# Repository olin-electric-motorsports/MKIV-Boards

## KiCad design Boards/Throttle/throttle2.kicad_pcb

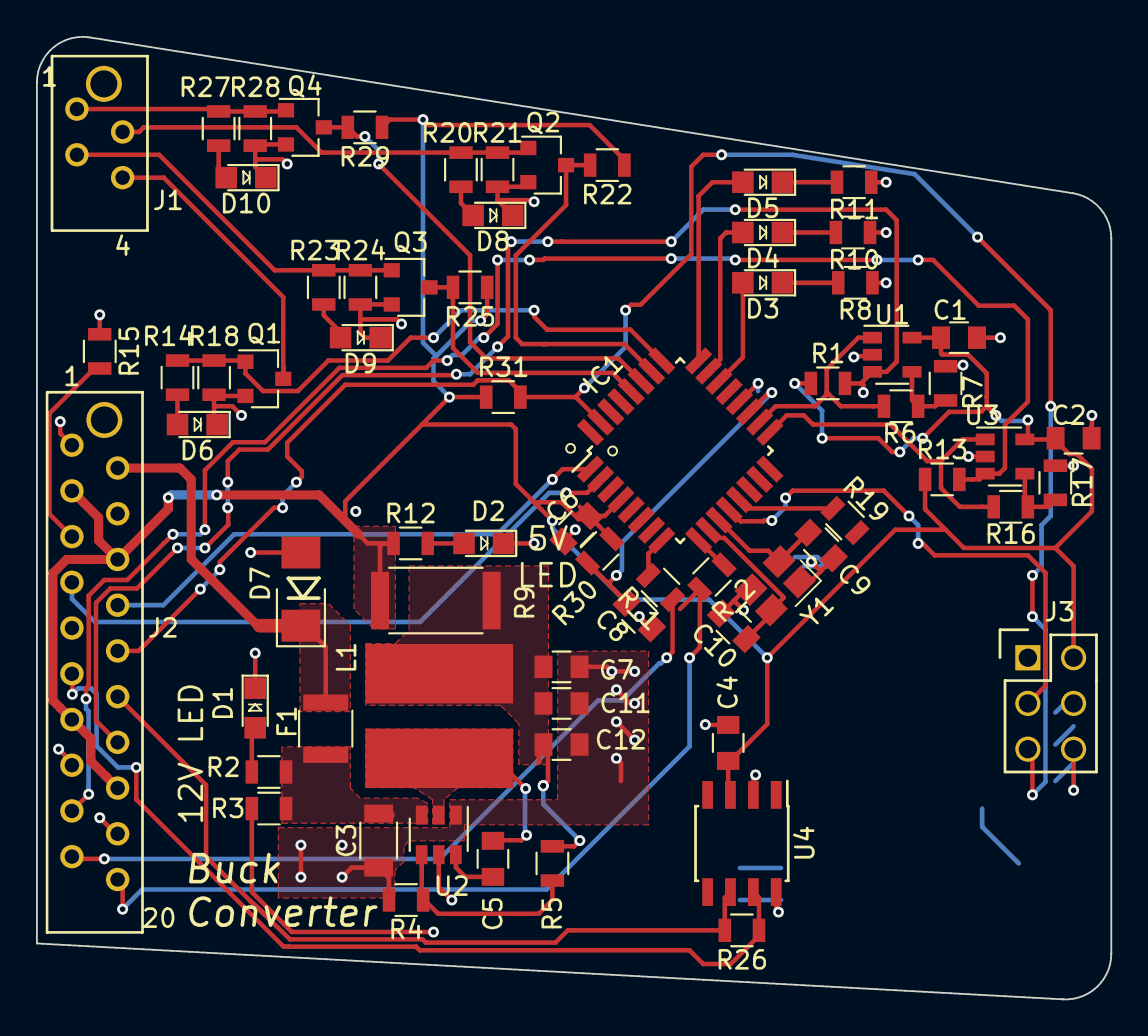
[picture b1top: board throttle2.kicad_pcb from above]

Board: 2 copper layers, 59.7 x 53.5 mm, 70 parts (0 on the bottom side), 52 nets.

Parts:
C1, C2, C4, C5, C6, C7: C_0.1uF; C_0805_OEM
C3: C_22uF; C_1206_OEM
C8: C_100pF; C_0805_OEM
C9, C10: C_30pF; C_0805_OEM
C11: C_1uF; C_0805_OEM
C12: C_47uF; C_0805_OEM
D1, D2, D3, D4, D5, D6, D8, D9, D10: LED_0805; LED_0805_OEM
D7: D_Zener_18V; DO-214AA
F1: 500mA; Fuse_1210
IC1: ATMEGA16M1; TQFP-32_7x7mm_Pitch0.8mm
J1: micromatch_female_TOP_ENTRY_locking_4; micromatch_female_vert_4
J2: micromatch_female_TOP_ENTRY_locking_20; micromatch_female_vert_20
J3: CONN_02X03; Pin_Header_Straight_2x03
L1: L_4.7uH; 4.7uH_Inductor_OEM
Q1, Q2, Q3, Q4: SSM3K333R; SOT-23F
R1, R13: R_1M; R_0805_OEM
R2, R6, R20, R23, R27: R_1k; R_0805_OEM
R3, R4, R22, R25, R29, R31: R_10k; R_0805_OEM
R5: R_51.1k; R_0805_OEM
R7, R16, R17: R_2.2k; R_0805_OEM
R8, R10, R11, R12, R14: R_200; R_0805_OEM
R9: R_0_Jumper; R_2512_OEM
R15, R19: R_22K; R_0805_OEM
R18: R_100K; R_0805_OEM
R21, R24, R28: R_100k; R_0805_OEM
R26: R_120 DNP; R_0805_OEM
R30: R_100; R_0805_OEM
R_1, R_2: R_200; R_0805_OEM
U1, U3: MCP6001; SOT-23-5_OEM
U2: TPS561201; SOT-23-6_OEM
U4: CAN_Transceiver; SOIC-8_3.9x4.9mm_Pitch1.27mm_OEM
Y1: Crystal_SMD; Crystal_SMD_FA238

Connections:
+12V: D7.1, F1.1, J2.2
/12V_Fused: C3.1, F1.2, R2.1, R3.1, U2.3
/CANH: J2.11, R26.1, U4.7
/CANL: J2.12, R26.2, U4.6
/Drive_Mode_Out: IC1.13, J2.4, R19.1
/GND_DriveMode: J2.5, R15.2
/LED1: J2.19, R_1.1
/LED2: J2.20, R_2.1
/MISO: IC1.1, J2.8, J3.1
/MOSI: IC1.2, J2.7, J3.4
/ProgrammingLED1: D3.2, IC1.22
/ProgrammingLED2: D4.2, IC1.23
/ProgrammingLED3: D5.2, IC1.24
/RESET: IC1.31, J2.10, J3.5, R31.2
/RTD: J1.4, Q1.3
/RXCAN: IC1.7, U4.4
/ReadyToDrive_LowDrive: IC1.25, Q1.1, R14.1, R18.1
/SCK: IC1.12, J2.9, J3.3
/SS_BOTS: J1.1, Q4.1, R27.1, R28.1
/SS_BOTS_Out_n: IC1.27, Q4.3, R29.2
/SS_Cockpit_EStop: J1.3, Q3.1, R23.1, R24.1
/SS_EStop_Out_n: IC1.28, Q3.3, R25.2
/SS_Inertia_Out_n: IC1.26, Q2.3, R22.2
/SS_Inertia_Switch: J1.2, Q2.1, R20.1, R21.1
/TXCAN: IC1.6, U4.1
/Throttle1Adjusted: IC1.17, R16.1, U3.1
/Throttle1_Right_Sense: J2.14, R1.2, U1.3
/Throttle2Adjusted: IC1.18, R6.1, U1.1
/Throttle2_Left_Sense: J2.17, R13.2, U3.3
GND: C1.1, C2.1, C3.2, C4.2, C6.2, C7.2, C8.2, C9.2, C10.2, C11.2, C12.2, D1.1, D2.1, D6.1, D7.2, D8.1, D9.1, D10.1, IC1.5, IC1.20, J2.1, J2.15, J2.18, J3.6, Q1.2, Q2.2, Q3.2, Q4.2, R4.2, R7.2, R8.2, R10.2, R11.2, R15.1, R17.2, R18.2, R19.2, R21.2, R24.2, R28.2, U1.2, U2.1, U3.2, U4.2, U4.8, Y1.2, Y1.4
unnamed: C5.1, U2.6
unnamed: C5.2, L1.1, U2.2
unnamed: C8.1, IC1.19, R30.2
unnamed: C9.1, IC1.11, Y1.1
unnamed: C10.1, IC1.10, Y1.3
unnamed: C7.1, C11.1, C12.1, L1.2, R5.2, R9.2
unnamed: D1.2, R2.2
unnamed: D2.2, R12.2
unnamed: D3.1, R8.1
unnamed: D4.1, R10.1
unnamed: D5.1, R11.1
unnamed: D6.2, R14.2
unnamed: D8.2, R20.2
unnamed: D9.2, R23.2
unnamed: D10.2, R27.2
unnamed: IC1.8, R_1.2
unnamed: IC1.9, R_2.2
unnamed: R3.2, U2.5
unnamed: R4.1, R5.1, U2.4
unnamed: R6.2, R7.1, U1.4
unnamed: R16.2, R17.1, U3.4
VCC: C1.2, C2.2, C4.1, C6.1, IC1.4, J2.3, J2.6, J2.13, J2.16, J3.2, R1.1, R9.1, R12.1, R13.1, R22.1, R25.1, R29.1, R30.1, R31.1, U1.5, U3.5, U4.3

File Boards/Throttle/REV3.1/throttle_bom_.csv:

Component,Description,Part,References,Value,Footprint,Quantity Per PCB,Datasheet,Package,MPN,MFN,PurchasingLink,Purchase_Link
1,"Capacitor, 0.1uF, 50V, 5%, 0805",C_0.1uF,C1 C2 C4 C5 C6 C7,C_0.1uF,C_0805_OEM,6,http://datasheets.avx.com/X7RDielectric.pdf,Value,478-3352-1-ND,DK,https://www.digikey.com/products/en?keywords=478-3352-1-ND,
2,"Capacitor, 100pF, 50V, 5%, 0805",C_100pF,C8,C_100pF,C_0805_OEM,1,https://katalog.we-online.de/pbs/datasheet/885012007057.pdf,Value,732-7852-1-ND,DK,https://www.digikey.com/product-detail/en/wurth-electronics-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,
3,"Capacitor, 1uF, 25V, 10%, 0805",C_1uF,C11,C_1uF,C_0805_OEM,1,http://www.samsungsem.com/kr/support/product-search/mlcc/__i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,Value,1276-2887-1-ND,DK,https://www.digikey.com/product-detail/en/samsung-electro-me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,
4,"Capacitor, 22uF, 16V, 20%, 1206",C_22uF,C3,C_22uF,C_1206_OEM,1,https://product.tdk.com/info/en/catalog/datasheets/mlcc_comm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,Value,445-11693-1-ND,DK,https://www.digikey.com/product-detail/en/tdk-corporation/C3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,
5,"Capacitor, 30pF, 50V, 5%, 0805",C_30pF,C9 C10,C_30pF,C_0805_OEM,2,https://media.digikey.com/pdf/Data%20Sheets/Samsung%20PDFs/C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,Value,1276-1130-1-ND,DK,https://www.digikey.com/product-detail/en/samsung-electro-me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,
6,"Capacitor, 47uF, 6.3V, 20%, 0805",C_47uF,C12,C_47uF,C_0805_OEM,1,http://www.samsungsem.com/kr/support/product-search/mlcc/__i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,Value,1276-6467-1-ND,DK,https://www.digikey.com/product-detail/en/samsung-electro-me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,
7,"Diode, Zener, 18V, 5W, 5%",D_Zener_18V,D7,D_Zener_18V,DO-214AA,1,http://www.mccsemi.com/up_pdf/SMBJ5338B-SMBJ5388B(SMB).pdf,DO-214AA (SMB),SMBJ5355B-TPMSCT-ND,DK,https://www.digikey.com/products/en?keywords=SMBJ5355B-TPMSCT-ND,
8,"LED, Green, 2.2V, 20mA, 0805",LED_0805,D1 D2 D3 D4 D5 D6 D8 D9 D10,LED_0805,LED_0805_OEM,9,http://www.osram-os.com/Graphics/XPic9/00078860_0.pdf,Value,475-1410-1-ND,DK,https://www.digikey.com/products/en?keywords=475-1410-1-ND,
9,"Fuse, PTC, 500mA, 16V, 1210",F_500mA_16V,F1,500mA,Fuse_1210,1,https://belfuse.com/resources/CircuitProtection/datasheets/0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,Value,507-1786-1-ND,DK,https://www.digikey.com/product-detail/en/bel-fuse-inc/0ZCH0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,
10,"Microcontroller, 8-bit, 1KB RAM, 16KB Flash",ATMEGA16M1,IC1,ATMEGA16M1,TQFP-32_7x7mm_Pitch0.8mm,1,http://ww1.microchip.com/downloads/en/DeviceDoc/Atmel-8209-8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,Value,ATMEGA16M1-AU-ND,DK,https://www.digikey.com/product-detail/en/atmel/ATMEGA16M1-A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,
11,"Connector header through hole 2x3 0.100"" (2.54mm)",CONN_02X03,J3,CONN_02X03,Pin_Header_Straight_2x03,1,http://portal.fciconnect.com/Comergent//fci/drawing/67996.pdf,Value,609-3234-ND,DK,https://www.digikey.com/product-detail/en/amphenol-fci/67997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,
12,Micro-MaTch connector 20 pin female vertical,MM_F_VT_20,J2,micromatch_female_TOP_ENTRY_locking_20,micromatch_female_vert_20,1,http://www.te.com/commerce/DocumentDelivery/DDEController?Ac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,Value,2-338068-0,TE,http://www.te.com/global-en/product-2-338068-0.html,
13,Micro-MaTch connector 4 pin female vertical,MM_F_VT_04,J1,micromatch_female_TOP_ENTRY_locking_4,micromatch_female_vert_4,1,http://www.te.com/commerce/DocumentDelivery/DDEController?Ac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,Value,338068-4,TE,http://www.te.com/global-en/product-338068-4.html,
14,"Inductor, 4.7uH, 4.4A, 25mOhm, 20%",L_4.7uH,L1,L_4.7uH,4.7uH_Inductor_OEM,1,https://product.tdk.com/info/en/documents/wdcatalog/withdraw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,Value,445-6583-1-ND,DK,https://www.digikey.com/product-detail/en/tdk-corporation/VL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,
15,"MOSFET, N-channel, 30V, 6A",SSM3K333R,Q1 Q2 Q3 Q4,SSM3K333R,SOT-23F,4,https://drive.google.com/drive/folders/0B-V-iZf33Y4GNzhDQTJZanJRbVk,SOT-23-3 Flat Leads,SSM3K333RLFCT-ND,DK,https://www.digikey.com/product-detail/en/toshiba-semiconduc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,https://www.digikey.com/product-detail/en/toshiba-semiconduc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
16,"Resistor, 0 ohm jumper, 0.1W, 0603",R_0,R9,R_0_Jumper,R_0603_1608Metric,1,http://industrial.panasonic.com/www-cgi/jvcr13pz.cgi?E+PZ+3+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,Value,P0.0GCT-ND,DK,https://www.digikey.com/product-detail/en/panasonic-electron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,
17,"Resistor, 100, 0.25W, 1%, 0805",R_100,R30,R_100,R_0805_OEM,1,https://www.seielect.com/Catalog/SEI-rncp.pdf,Value,RNCP0805FTD100RCT-ND,DK,https://www.digikey.com/products/en?keywords=RNCP0805FTD100RCT-ND,
18,"Resistor, 100K, 0.125W, 1%, 0805",R_100K,R18 R21 R24 R28,R_100K,R_0805_OEM,4,https://industrial.panasonic.com/cdbs/www-data/pdf/RDA0000/A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,Value,P100KCCT-ND,DK,https://www.digikey.com/product-detail/en/panasonic-electron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,
19,"Resistor, 10K, 0.25W, 1%, 0805",R_10K,R22 R25 R29 R31,R_10k,R_0805_OEM,4,http://www.bourns.com/data/global/pdfs/CRS.pdf,Value,CRS0805-FX-1002ELFCT-ND,DK,https://www.digikey.com/products/en?keywords=CRS0805-FX-1002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,
20,"Resistor, 10K, 5W, 1%, Axial",R_10K_HV,R3 R4,R_10k,R_0805_OEM,2,http://www.vishay.com/docs/28731/pacserie.pdf,Value,PPC5D10.0KCT-ND,DK,https://www.digikey.com/products/en?keywords=PPC5D10.0KCT-ND,
21,"Resistor, 120K, 0.125W, 1%, 0805",R_120K,R26,R_120 DNP,R_0805_OEM,1,https://www.seielect.com/Catalog/SEI-RMCF_RMCP.pdf,Value,RMCF0805JT200RCT-ND,DK,https://www.digikey.com/products/en?keywords=RMCF0805JT200RCT-ND,
22,"Resistor, 1M, 0.125W, 5%, 0805",R_1M,R1 R13,R_1M,R_0805_OEM,2,https://www.seielect.com/Catalog/SEI-rncp.pdf,Value,RMCF0805JT1M00CT-ND,DK,https://www.digikey.com/product-detail/en/stackpole-electron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,
23,"Resistor, 1K, 0.25W, 1%, 0805",R_1K,R2 R6 R20 R23 R27,R_1k,R_0805_OEM,5,https://www.seielect.com/Catalog/SEI-rncp.pdf,Value,RNCP0805FTD1K00CT-ND,DK,https://www.digikey.com/products/en?keywords=RNCP0805FTD1K00CT-ND,
24,"Resistor, 2.2K, 0.125W, 1%, 0805",R_2.2K,R7 R16 R17,R_2.2k,R_0805_OEM,3,https://www.seielect.com/Catalog/SEI-RMCF_RMCP.pdf,Value,RMCF0805FT2K20CT-ND,DK,https://www.digikey.com/product-detail/en/stackpole-electron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,
25,"Resistor, 200, 0.125W, 5%, 0805",R_200,R8 R10 R11 R12 R14 R_1 R_2,R_200,R_0805_OEM,7,https://www.seielect.com/Catalog/SEI-RMCF_RMCP.pdf,Value,RMCF0805JT200RCT-ND P100KCCT-ND,DK,https://www.digikey.com/products/en?keywords=RMCF0805JT200RCT-ND https://www.digikey.com/product-detail/en/panasonic-electron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,
26,"Resistor, 22K, 0.125W, 5%, 0805",R_22K,R15 R19,R_22K,R_0805_OEM,2,https://www.seielect.com/Catalog/SEI-RMCF_RMCP.pdf,,RMCF0805JT22K0CT-ND,DK,https://www.digikey.com/products/en?keywords=RMCF0805JT22K0CT-ND,
27,"Resistor, 51.1K, 0.125W, 1%, 0805",R_51.1K,R5,R_51.1k,R_0805_OEM,1,https://industrial.panasonic.com/cdbs/www-data/pdf/RDA0000/A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,Value,P51.1KCCT-ND,DK,https://www.digikey.com/product-detail/en/panasonic-electron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,
28,"High speed CAN transceiver, 1Mb/s",MCP2561-E_SN,U4,CAN_Transceiver,SOIC-8_3.9x4.9mm_Pitch1.27mm_OEM,1,http://www.microchip.com/mymicrochip/filehandler.aspx?ddocna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,Value,MCP2561-E/SN-ND,DK,https://www.digikey.com/products/en?keywords=mcp2561-e%2Fsn,
29,"Op-amp, general purpose",MCP6001,U1 U3,MCP6001,SOT-23-5_OEM,2,http://ww1.microchip.com/downloads/en/DeviceDoc/21733j.pdf,Value,MCP6001T-I/OTCT-ND,N/A,https://www.digikey.com/product-detail/en/microchip-technolo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,
30,"Buck converter, 4.5-17V input, adj 0.76-7V output, 1A, 580kHz",TPS561201,U2,TPS561201,SOT-23-6_OEM,1,http://www.ti.com/lit/ds/symlink/tps561201.pdf,Value,TPS561201,DK,https://www.digikey.com/products/en?keywords=296-46928-1-ND,
31,CRYSTAL 16.0000MHZ 18PF SMD,Crystal_SMD,Y1,Crystal_SMD,Crystal_SMD_FA238,1,http://www.txccorp.com/download/products/quartz_crystals/201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,Value,887-1125-1-ND,DK,https://www.digikey.com/product-detail/en/txc-corporation/7M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,





Component Groups:,31
Component Count:,70
Fitted Components:,70
Number of PCBs:,1
Total components:,70
Schematic Version:,
Schematic Date:,
BoM Date:,Sat 01 Dec 2018 11:14:35 AM EST
Schematic Source:,/home/awenstrup/Documents/Formula/MKIV-Boards/Boards/Throttle/REV3.1/throttle.sch
KiCad Version:,Eeschema 5.0.1-33cea8e~68~ubuntu18.04.1

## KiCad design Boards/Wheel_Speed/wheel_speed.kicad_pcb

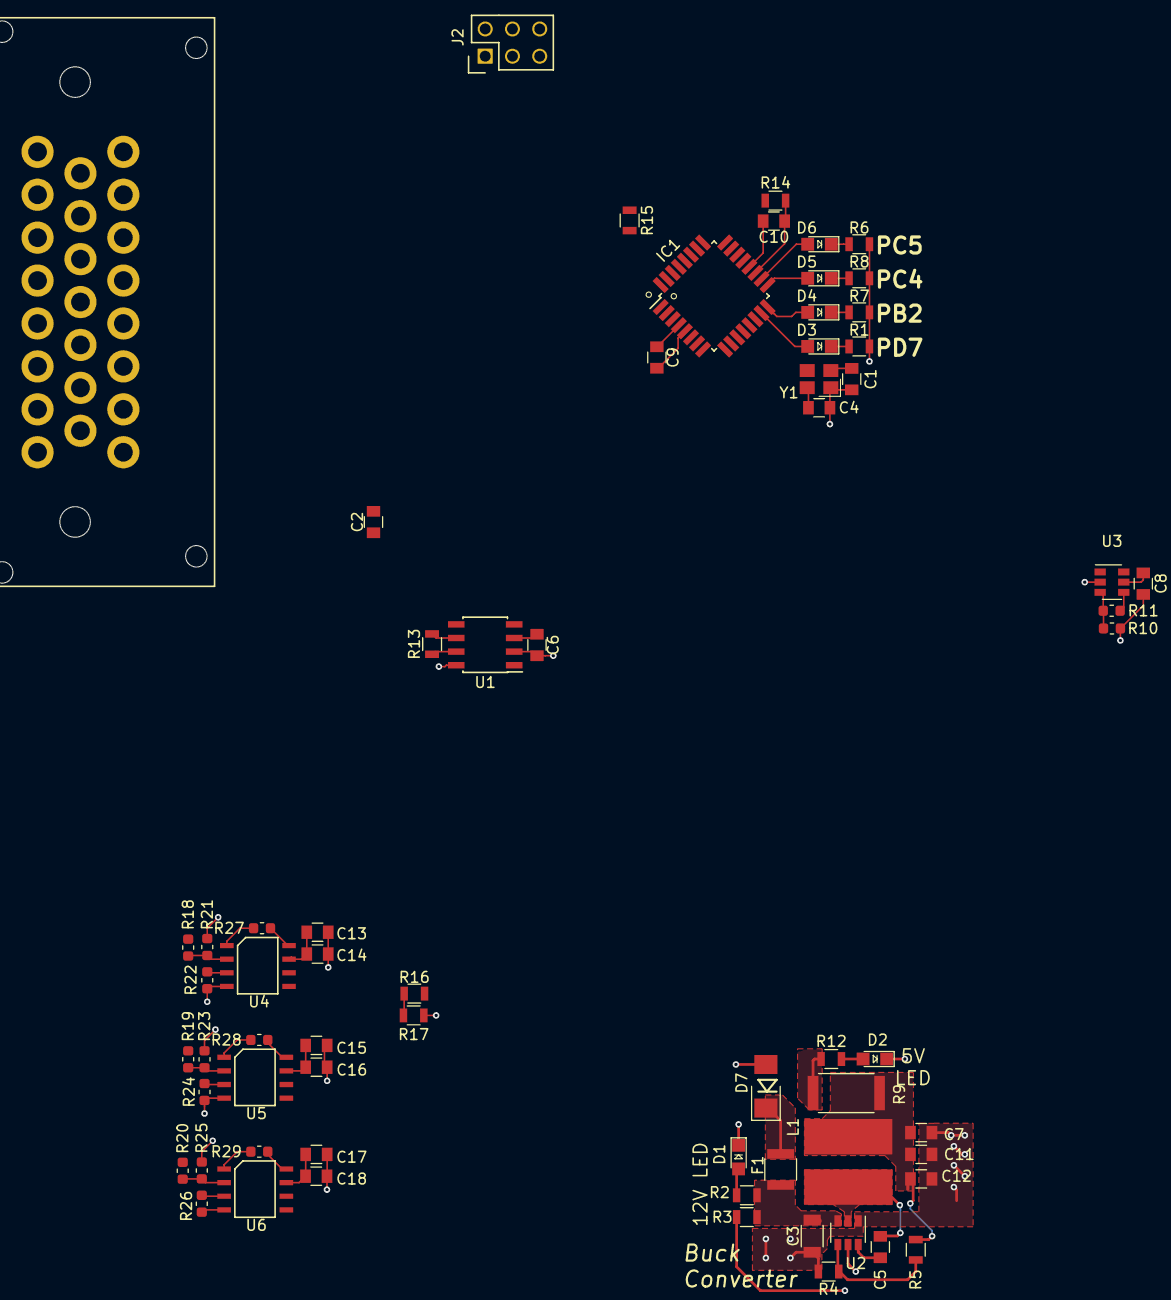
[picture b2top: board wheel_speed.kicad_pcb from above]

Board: 2 copper layers, 66 parts (0 on the bottom side), 51 nets.

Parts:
C1, C4: C_30pF; C_0805_OEM
C2, C5, C6, C8, C9, C12, C14, C16, C18: C_0.1uF; C_0805_OEM
C3: C_22uF; C_1206_OEM
C7: C_47uF; C_0805_OEM
C10: C_100pF; C_0805_OEM
C11: C_1uF; C_0805_OEM
C13, C15, C17: C_10uF; C_0805_OEM
D1, D2, D3, D4, D5, D6: LED_0805; LED_0805_OEM
D7: D_Zener_18V; DO-214AA
F1: 500mA; Fuse_1210
IC1: ATMEGA16M1; TQFP-32_7x7mm_Pitch0.8mm
J1: Ampseal_23_RA; Ampseal_23
J2: CONN_02X03; Pin_Header_Straight_2x03
L1: L_4.7uH; 4.7uH_Inductor_OEM
R1, R6, R7, R8, R12: R_200; R_0805_OEM
R2: R_1k; R_0805_OEM
R3, R4, R15: R_10k; R_0805_OEM
R5: R_51.1k; R_0805_OEM
R9: R_0_Jumper; R_2512_OEM
R10, R11, R18, R19, R20, R21, R22, R23, R24, R25, R26, R27, R28, R29: R_0; R_0603_1608Metric
R13: R_120; R_0805_OEM
R14: R_100; R_0805_OEM
R16, R17: R_10K; R_0805_OEM
U1: CAN_Transceiver; SOIC-8_3.9x4.9mm_Pitch1.27mm_OEM
U2: TPS561201; SOT-23-6_OEM
U3: LMV341; SOT-23-6
U4, U5, U6: AD623; AD623_SOIC-8
Y1: Crystal_SMD; Crystal_SMD_FA238

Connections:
+12V: D7.1, F1.1, J1.1
/12V_Fused: C3.1, F1.2, R2.1, R3.1, U2.3
/BRAKETEMP: IC1.27, J1.12
/CANH: J1.3, J1.17, R13.1, U1.7
/CANL: J1.4, J1.18, R13.2, U1.6
/HSENSOR: IC1.26, J1.13
/MISO: IC1.1, J2.1
/MOSI: IC1.2, J2.4
/POT: J1.11, U3.1
/POT_SIGNAL: IC1.22, R10.1, R11.2, U3.3
/P_LED_1: D3.2, IC1.15
/P_LED_2: D4.2, IC1.16
/P_LED_3: D5.2, IC1.17
/P_LED_4: D6.2, IC1.18
/RESET: IC1.31, J2.5, R15.2
/RXCAN: IC1.7, U1.4
/SCK: IC1.12, J2.3
/Suspension Strain Testing/2.5V: R16.2, R17.1, U4.5, U5.5, U6.5
/TXCAN: IC1.6, U1.1
GND: C1.2, C2.1, C3.2, C4.2, C6.2, C7.2, C8.2, C9.2, C10.2, C11.2, C12.2, C13.1, C14.1, C15.1, C16.1, C17.1, C18.1, D1.1, D2.1, D7.2, IC1.5, IC1.20, J1.2, J1.6, J2.6, R1.2, R4.2, R6.2, R7.2, R8.2, R10.2, R17.2, R21.1, R22.1, R23.1, R24.1, R25.1, R26.1, U1.2, U1.8, U2.1, U3.2, U4.4, U5.4, U6.4, Y1.2, Y1.4
unnamed: C1.1, IC1.11, Y1.1
unnamed: C4.1, IC1.10, Y1.3
unnamed: C5.1, U2.6
unnamed: C5.2, L1.1, U2.2
unnamed: C10.1, IC1.19, R14.2
unnamed: C7.1, C11.1, C12.1, L1.2, R5.2, R9.2
unnamed: D1.2, R2.2
unnamed: D2.2, R12.2
unnamed: D3.1, R1.1
unnamed: D4.1, R7.1
unnamed: D5.1, R8.1
unnamed: D6.1, R6.1
unnamed: R3.2, U2.5
unnamed: R4.1, R5.1, U2.4
unnamed: R11.1, U3.4
unnamed: R18.1, R21.2, U4.2
unnamed: R19.1, R23.2, U5.2
unnamed: R20.1, R25.2, U6.2
unnamed: R27.1, U4.8
unnamed: R27.2, U4.1
unnamed: R28.1, U5.8
unnamed: R28.2, U5.1
unnamed: R29.1, U6.8
unnamed: R29.2, U6.1
VCC: C2.2, C6.1, C8.1, C9.1, C13.2, C14.2, C15.2, C16.2, C17.2, C18.2, IC1.4, J1.5, J2.2, R9.1, R12.1, R14.1, R15.1, R16.1, R18.2, R19.2, R20.2, U1.3, U3.5, U4.7, U5.7, U6.7
gauge1.1in: J1.14, R22.2, U4.3
gauge1.1out: IC1.28, U4.6
gauge1.2in: J1.15, R24.2, U5.3
gauge1.2out: IC1.13, U5.6
gauge1.3in: J1.16, R26.2, U6.3
gauge1.3out: IC1.14, U6.6

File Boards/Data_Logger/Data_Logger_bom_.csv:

Component,Description,Part,References,Value,Footprint,Quantity Per PCB,Datasheet,Package,MPN,MFN,PurchasingLink,Purchasing Link
1,"Capacitor, 0.1uF, 50V, 5%, 0805",C_0.1uF,C1 C4 C5 C9 C10 C12 C15 C16,C_0.1uF,C_0805_OEM,8,http://datasheets.avx.com/X7RDielectric.pdf,Value,478-3352-1-ND,Digi-Key DK,https://www.digikey.com/products/en?keywords=478-3352-1-ND,
2,"Capacitor, 100pF, 50V, 5%, 0805",C_100pF,C2,C_100pF,C_0805_OEM,1,https://content.kemet.com/datasheets/KEM_C1003_C0G_SMD.pdf,Value,399-1122-1-ND,Digi-Key,https://www.digikey.com/product-detail/en/kemet/C0805C101J5G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,
3,"Capacitor, 10uF, 10V, 10%, 0805",C_10uF,C13,C_10uF,C_0805_OEM,1,http://www.samsungsem.com/kr/support/product-search/mlcc/__i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,,1276-1052-1-ND,DK,https://www.digikey.com/product-detail/en/samsung-electro-me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,
4,"Capacitor, 1uF, 25V, 10%, 0805",C_1uF,C11 C14,C_1uF,C_0805_OEM,2,http://datasheets.avx.com/X7RDielectric.pdf,Value,478-10487-1-ND 1276-2887-1-ND,Digi-Key DK,https://www.digikey.com/product-detail/en/avx-corporation/08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 https://www.digikey.com/product-detail/en/samsung-electro-me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,
5,"Capacitor, 22uF, 16V, 20%, 1206",C_22uF,C3,C_22uF,C_1206_OEM,1,http://www.samsungsem.com/kr/support/product-search/mlcc/__i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,Value,1276-2725-1-ND,Digi-Key,https://www.digikey.com/products/en?keywords=1276-2725-1-ND,
6,"Capacitor, 30pF, 50V, 5%, 0805",C_30pF,C6 C8,C_30pF,C_0805_OEM,2,https://media.digikey.com/pdf/Data%20Sheets/Samsung%20PDFs/C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,Value,1276-1130-1-ND,Digi-Key,https://www.digikey.com/product-detail/en/samsung-electro-me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,
7,"Capacitor, 47uF, 6.3V, 20%, 0805",C_47uF,C7,C_47uF,C_0805_OEM,1,http://www.yuden.co.jp/productdata/catalog/en/mlcc_all_e.pdf,Value,587-4280-1-ND,Digi-Key,https://www.digikey.com/product-detail/en/taiyo-yuden/JMK212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,
8,"Diode, Zener, 18V, 5W, 5%",D_Zener_18V,D7,D_Zener_18V,DO-214AA,1,http://www.mccsemi.com/up_pdf/SMBJ5338B-SMBJ5388B(SMB).pdf,DO-214AA (SMB),SMBJ5355B-TPMSCT-ND,Digi-Key,https://www.digikey.com/products/en?keywords=SMBJ5355B-TPMSCT-ND,
9,"LED, Green, 2.2V, 20mA, 0805",LED_0805,D1 D2 D3 D4 D5,LED_0805,LED_0805_OEM,5,http://www.osram-os.com/Graphics/XPic9/00078860_0.pdf,Value,475-1410-1-ND,Digi-Key DK,https://www.digikey.com/products/en?keywords=475-1410-1-ND,
10,"Fuse, PTC, 500mA, 16V, 1210",F_500mA_16V,F1,500mA,Fuse_1210,1,https://belfuse.com/resources/CircuitProtection/datasheets/0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,Value,507-1786-1-ND,Digi-Key,https://www.digikey.com/product-detail/en/bel-fuse-inc/0ZCH0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,
11,"Microcontroller, 8-bit, 1KB RAM, 16KB Flash",ATMEGA16M1,IC1,ATMEGA16M1,TQFP-32_7x7mm_Pitch0.8mm,1,http://www.atmel.com/Images/Atmel-8209-8-bit%20AVR%20ATmega1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,Value,ATMEGA16M1-AU-ND,Digi-Key,https://www.digikey.com/product-detail/en/atmel/ATMEGA16M1-A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,
12,"Connector header through hole 2x3 0.100"" (2.54mm)",CONN_02X03,J4,CONN_02X03,Pin_Header_Straight_2x03,1,http://portal.fciconnect.com/Comergent//fci/drawing/67996.pdf,Value,609-3234-ND,Digi-Key,https://www.digikey.com/product-detail/en/amphenol-fci/67997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,
13,"Generic connector, single row, 01x03, script generated (kicad-library-utils/schlib/autogen/connector/)",Conn_01x03,J2,Conn_01x03,PinHeader_1x03_P2.54mm_Vertical,1,~,,,,,
14,Micro-MaTch connector 20 pin female right angle,MM_F_RA_20,J3,MM_F_RA_20,micromatch_female_ra_20,1,http://www.te.com/commerce/DocumentDelivery/DDEController?Ac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,,2-338070-0,TE,http://www.te.com/usa-en/product-2-338070-0.html,
15,SD card socket with detect switch,SD_socket,J1,SD_socket,sd_socket_molex_5009980900,1,https://www.molex.com/pdm_docs/sd/5009980900_sd.pdf,,WM24032CT-ND,DK,https://www.digikey.com/product-detail/en/molex-llc/50099809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,
16,"Inductor, 4.7uH, 4.4A, 25mOhm, 20%",L_4.7uH,L1,L_4.7uH,4.7uH_Inductor_OEM,1,https://product.tdk.com/info/en/documents/wdcatalog/withdraw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,Value,445-6583-1-ND,Digi-Key,https://www.digikey.com/product-detail/en/tdk-corporation/VL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,
17,"Resistor, 0 ohm jumper, 0.1W, 0603",R_0,R9,R_0_Jumper,R_2512_OEM,1,http://www.te.com/commerce/DocumentDelivery/DDEController?Ac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,Value,A121322CT-ND,Digi-Key,https://www.digikey.com/products/en?keywords=A121322CT-ND,
18,"Resistor, 100, 0.25W, 1%, 0805",R_100,R1,R_100,R_0805_OEM,1,https://www.seielect.com/Catalog/SEI-rncp.pdf,Value,RNCP0805FTD100RCT-ND,Digi-Key,https://www.digikey.com/products/en?keywords=RNCP0805FTD100RCT-ND,
19,"Resistor, 10K, 0.25W, 1%, 0805",R_10K,R8 R13 R14 R15 R16 R17,R_10k,R_0805_OEM,6,http://www.bourns.com/data/global/pdfs/CRS.pdf,Value,CRS0805-FX-1002ELFCT-ND,Digi-Key DK,https://www.digikey.com/products/en?keywords=CRS0805-FX-1002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,
20,"Resistor, 10K, 5W, 1%, Axial",R_10K_HV,R3 R4,R_10k,R_0805_OEM,2,http://www.bourns.com/data/global/pdfs/CRS.pdf,Value,CRS0805-FX-1002ELFCT-ND,Digi-Key,https://www.digikey.com/products/en?keywords=CRS0805-FX-1002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,
21,"Resistor, 120, 0.125W, 1%, 0805",R_120,R7,R_120,R_0805_OEM,1,https://www.mouser.com/datasheet/2/315/AOA0000C304-1149620.pdf,,667-ERJ-6ENF1200V,DK,https://www.mouser.com/ProductDetail/Panasonic-Industrial-De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,
22,"Resistor, 1K, 0.25W, 1%, 0805",R_1K,R2,R_1k,R_0805_OEM,1,https://www.seielect.com/Catalog/SEI-rncp.pdf,Value,RNCP0805FTD1K00CT-ND,Digi-Key,https://www.digikey.com/products/en?keywords=RNCP0805FTD1K00CT-ND,
23,"Resistor, 200, 0.125W, 5%, 0805",R_200,R6 R10 R11 R12 R18 R19,R_200,R_0805_OEM,6,https://www.seielect.com/Catalog/SEI-RMCF_RMCP.pdf,Value,RMCF0805JT200RCT-ND,DK Digi-Key,https://www.digikey.com/products/en?keywords=RMCF0805JT200RCT-ND,
24,"Resistor, 51.1K, 0.125W, 1%, 0805",R_51.1K,R5,R_51.1k,R_0805_OEM,1,http://www.yageo.com.tw/exep/pages/download/literatures/PYu-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,Value,311-51.1KCRCT-ND,Digi-Key,https://www.digikey.com/products/en?keywords=311-51.1KCRCT-ND,
25,Slider Switch,MHSS1105,S1,MHSS1105,MHSS1105,1,https://www.apem.com/us/index.php?controller=attachment&id_a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,,679-1849-ND,APEM Inc.,,https://www.digikey.com/product-detail/en/apem-inc/MHSS1105/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
26,"High speed CAN transceiver, 1Mb/s",MCP2561-E_SN,U1,CAN_Transceiver,SOIC-8_3.9x4.9mm_Pitch1.27mm_OEM,1,http://www.microchip.com/mymicrochip/filehandler.aspx?ddocna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,Value,MCP2561-E/SN-ND,Digi-Key,https://www.digikey.com/products/en?keywords=mcp2561-e%2Fsn,
27,"Buck converter, 4.5-17V input, adj 0.76-7V output, 1A, 580kHz",TPS561201,U2,TPS561201,SOT-23-6_OEM,1,http://www.ti.com/lit/ds/symlink/tps561201.pdf,Value,TPS561201,Digi-Key,https://www.digikey.com/products/en?keywords=296-46928-1-ND,
28,"Voltage level translator, 4-channel, bidirectional, TSSOP-14",TXB0104,U3,TXB0104,TSSOP-14_4.4x5mm_P0.65mm,1,http://www.ti.com/lit/ds/symlink/txb0104.pdf,,296-21929-1-ND,DK,https://www.digikey.com/product-detail/en/texas-instruments/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,
29,CRYSTAL 16.0000MHZ 18PF SMD,Crystal_SMD,Y1,Crystal_SMD,Crystal_SMD_FA238,1,https://support.epson.biz/td/api/doc_check.php?dl=brief_FA-2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,Value,SER3686CT-ND,Digi-Key,https://www.digikey.com/products/en?keywords=SER3686CT-ND,





Component Groups:,29
Component Count:,53
Fitted Components:,53
Number of PCBs:,1
Total components:,53
Schematic Version:,
Schematic Date:,
BoM Date:,Thu 31 Jan 2019 08:48:02 PM EST
Schematic Source:,/home/thomas/Documents/Formula/MKIV-Boards/Boards/Data_Logger/Data_Logger.sch
KiCad Version:,Eeschema 5.0.2-bee76a0~70~ubuntu18.04.1

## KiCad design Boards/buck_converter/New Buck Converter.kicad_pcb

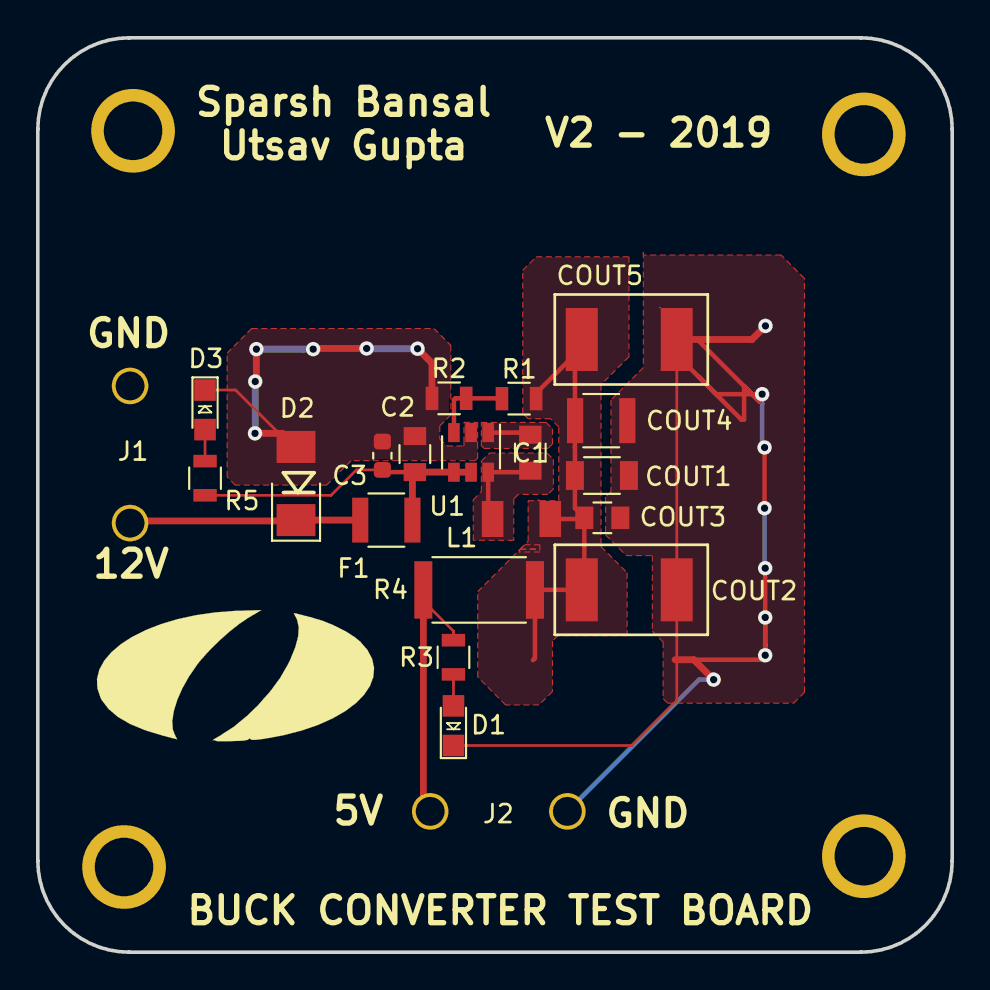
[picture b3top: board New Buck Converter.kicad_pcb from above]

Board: 2 copper layers, 50.8 x 50.8 mm, 21 parts (0 on the bottom side), 10 nets.

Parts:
C1, C2: C_0.1uF; C_0805_OEM
C3: C_2.2uF; C_0603_1608Metric
COUT1: C_22uF; C_1206_OEM
COUT2: C_33uF; Fuse_1812
COUT3: C_47uF; C_0805_OEM
COUT4: C_68uF; Fuse_1210
COUT5: C_100uF; Fuse_1812
D1, D3: LED_0805; LED_0805_OEM
D2: D_Zener_18V; DO-214AA
F1: F_500mA_16V; Fuse_1210
J1, J2: Conn_01x02_Female; 2-pin-throughhole-conn
L1: L_100uH
R1: R_100K; R_0805_OEM
R2: R_25K; R_0805_OEM
R3, R5: R_200; R_0805_OEM
R4: R_0_2512; R_2512_OEM
U1: TPS560430YF; SOT-23-6_OEM

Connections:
/12V: D2.1, F1.2, J1.2
GND: C2.2, C3.2, COUT1.2, COUT2.2, COUT3.2, COUT4.2, COUT5.2, D1.1, D2.2, D3.1, J1.1, J2.1, R2.2, U1.2
unnamed: C1.1, L1.1, U1.6
unnamed: C1.2, U1.1
unnamed: C2.1, C3.1, F1.1, R5.1, U1.4, U1.5
unnamed: COUT1.1, COUT2.1, COUT3.1, COUT4.1, COUT5.1, L1.2, R1.1, R4.1
unnamed: D1.2, R3.2
unnamed: D3.2, R5.2
unnamed: R1.2, R2.1, U1.3
VCC: R3.1, R4.2

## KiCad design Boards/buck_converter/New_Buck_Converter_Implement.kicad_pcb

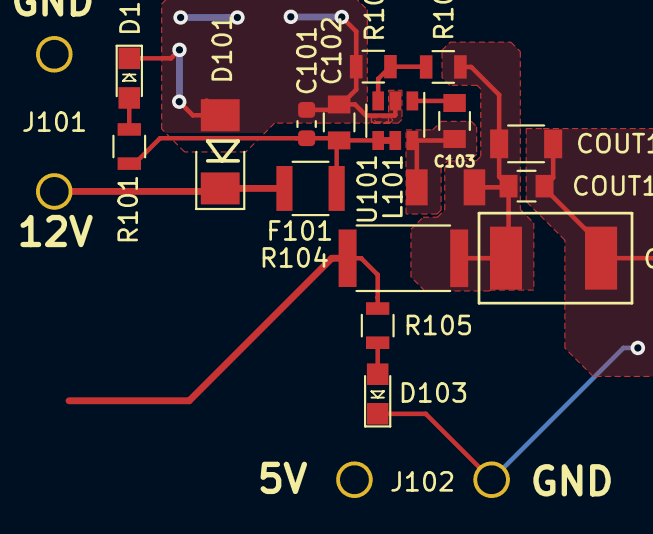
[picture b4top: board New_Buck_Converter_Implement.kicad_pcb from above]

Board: 2 copper layers, 19 parts (0 on the bottom side), 10 nets.

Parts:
C101: C_0.1uF; C_0603_1608Metric
C102: C_2.2uF; C_0805_OEM
C103: C_0.1uF; C_0805_OEM
COUT101: C_22uF; C_1206_OEM
COUT102: C_33uF; Fuse_1812
COUT103: C_47uF; C_0805_OEM
D101: D_Zener_18V; DO-214AA
D102, D103: LED_0805; LED_0805_OEM
F101: F_500mA_16V; Fuse_1210
J101, J102: Conn_01x02_Female; 2-pin-throughhole-conn
L101: L_100uH
R101, R105: R_200; R_0805_OEM
R102: R_25K; R_0805_OEM
R103: R_100K; R_0805_OEM
R104: R_0_2512; R_2512_OEM
U101: TPS560430YF; SOT-23-6_OEM

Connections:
/12V: D101.1, F101.2, J101.2
GND: C101.2, C102.2, COUT101.2, COUT102.2, COUT103.2, D101.2, D102.1, D103.1, J101.1, J102.1, R102.2, U101.2
unnamed: C101.1, C102.1, F101.1, R101.1, U101.4, U101.5
unnamed: C103.1, L101.1, U101.6
unnamed: C103.2, U101.1
unnamed: COUT101.1, COUT102.1, COUT103.1, L101.2, R103.1, R104.1
unnamed: D102.2, R101.2
unnamed: D103.2, R105.2
unnamed: R102.1, R103.2, U101.3
VCC: R104.2, R105.1
